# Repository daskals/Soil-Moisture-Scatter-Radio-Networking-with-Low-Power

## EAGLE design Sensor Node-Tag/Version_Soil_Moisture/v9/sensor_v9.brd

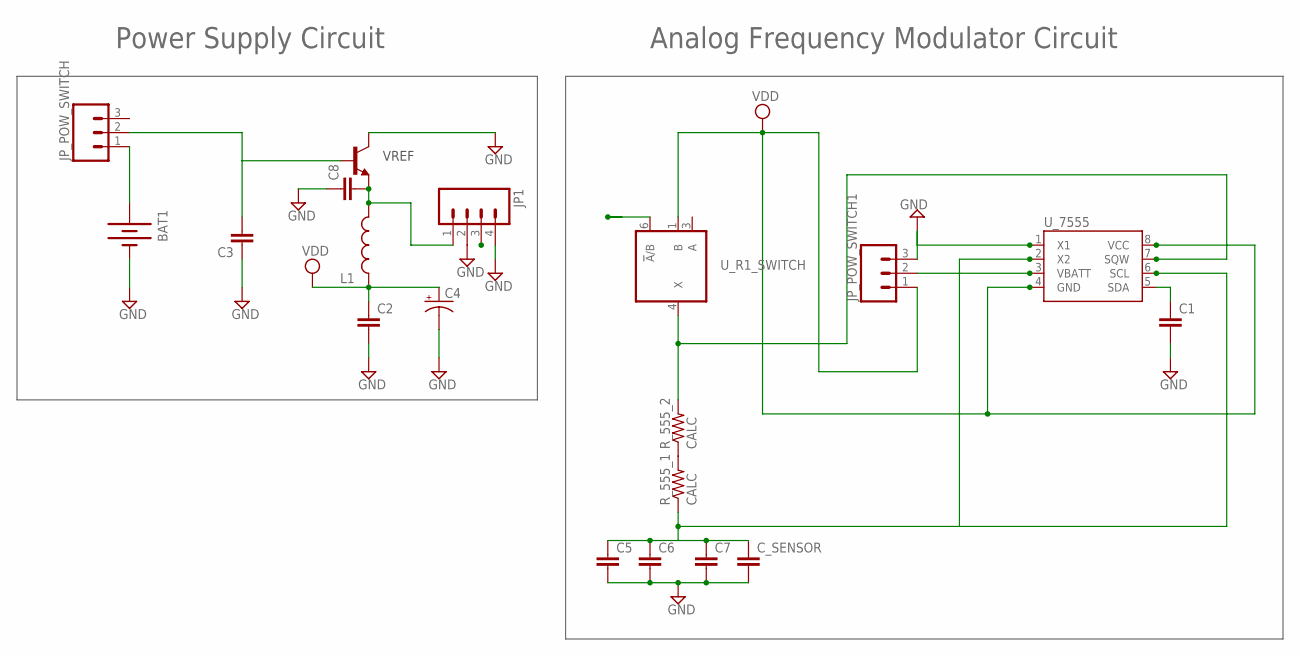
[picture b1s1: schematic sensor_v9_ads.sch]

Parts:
BAT1: BATTERY20PTH_LAB; BATTCOM_20MM_PTH
C1, C2, C3, C8: CAP0603-CAP; 0603-CAP
C4: CAP_POL1206; EIA3216
C5, C6, C7: CAP0805; 0805
C_SENSOR: CAP0805; 0805
JP1: M04LOCK; 1X04_LOCK
JP_POW_SWITCH, JP_POW_SWITCH1: M03LOCK; 1X03_LOCK
L1: INDUCTOR0603; 0603
R_555_1, R_555_2: CALC; 0805
U_7555: DS1307SO8; SO08
U_R1_SWITCH: 741G3157DCKR; DCK_R-PDSO-G6
U_VREF: TRANSISTOR_NPNSOT23-3; SOT23-3

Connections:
FOUT: JP_POW_SWITCH1.2, U_7555.3 (VBATT), U_R1_SWITCH.6 (!A!/B)
GND: BAT1.2 (-), C1.2, C2.2, C3.1, C4.C (-), C5.2, C6.2, C7.2, C8.1, C_SENSOR.2, JP1.2, JP1.4, JP_POW_SWITCH1.3, U_7555.1 (X1), U_R1_SWITCH.2 (GND), U_VREF.3 (C)
unnamed: BAT1.1 (+), JP1.3, JP_POW_SWITCH.1
unnamed: R_555_1.2, R_555_2.1
P2: C5.1, C6.1, C7.1, C_SENSOR.1, R_555_1.1, U_7555.2 (X2), U_7555.6 (SCL)
P5: C1.1, U_7555.5 (SDA)
P7: R_555_2.2, U_7555.7 (SQW), U_R1_SWITCH.4 (X)
VCC: U_R1_SWITCH.5 (VCC)
VDD: C2.1, C4.A (+), JP_POW_SWITCH1.1, L1.1, U_7555.4 (GND), U_7555.8 (VCC), U_R1_SWITCH.1 (B)
VREFIN: C3.2, JP_POW_SWITCH.2, U_VREF.1 (B)
VREFOUT: C8.2, JP1.1, L1.2, U_VREF.2 (E)

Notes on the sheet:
Power Supply Circuit
Analog Frequency Modulator Circuit
VREF

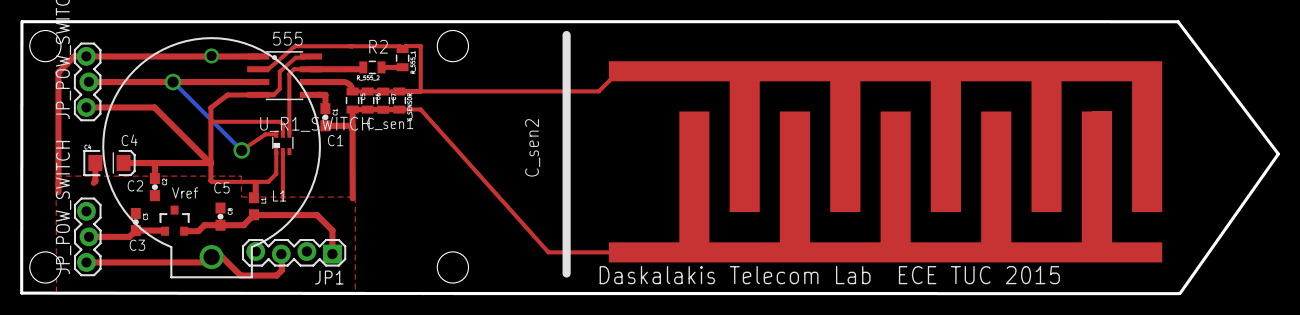
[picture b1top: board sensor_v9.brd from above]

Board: 2 copper layers, 124.9 x 27.0 mm, 19 parts (0 on the bottom side), 10 nets.

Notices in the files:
parts and their libraries:
SparkFun-Resistors: Licensing: CC v3.0 Share-Alike You are welcome to use this library for commercial purposes.
